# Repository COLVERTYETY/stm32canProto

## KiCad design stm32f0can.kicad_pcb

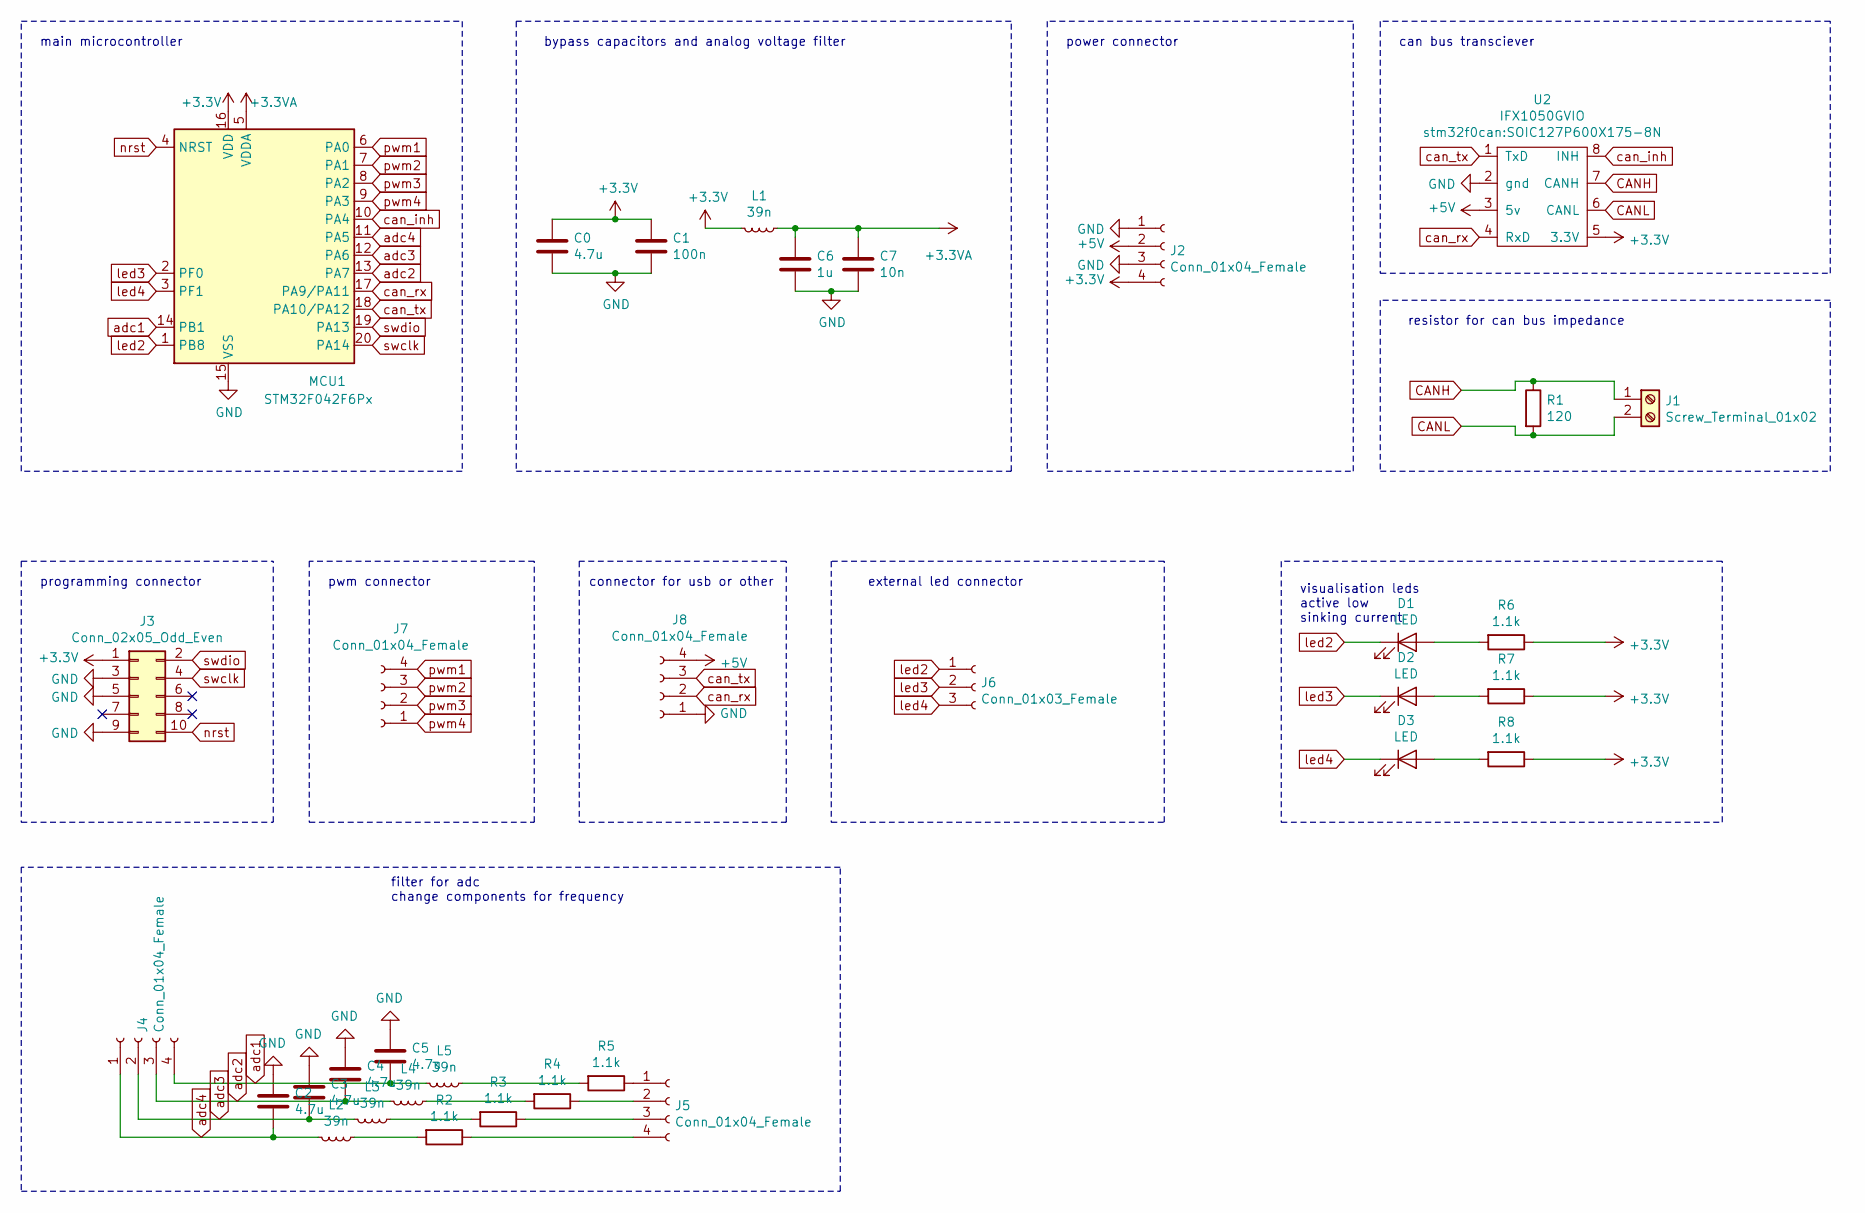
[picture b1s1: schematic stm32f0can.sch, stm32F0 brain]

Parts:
C0, C2, C3, C4, C5: 4.7u; CP_Radial_D6.3mm_P2.50mm
C1: 100n; CP_Radial_D6.3mm_P2.50mm
C6: 1u; CP_Radial_D6.3mm_P2.50mm
C7: 10n; CP_Radial_D6.3mm_P2.50mm
D1, D2, D3: LED; LED_D3.0mm
J1: Screw_Terminal_01x02; TerminalBlock_bornier-2_P5.08mm
J2, J4, J5, J7, J8: Conn_01x04_Female; PinHeader_1x04_P2.54mm_Vertical
J3: Conn_02x05_Odd_Even; PinHeader_2x05_P2.54mm_Vertical
J6: Conn_01x03_Female; PinHeader_1x04_P2.54mm_Vertical
L1, L2, L3, L4, L5: 39n; LairdTech_28C0236-0JW-10
MCU1: STM32F042F6Px; TSSOP-20_4.4x6.5mm_P0.65mm
R1: 120; R_Axial_DIN0204_L3.6mm_D1.6mm_P5.08mm_Vertical
R2, R3, R4, R5, R6, R7, R8: 1.1k; R_Axial_DIN0204_L3.6mm_D1.6mm_P5.08mm_Vertical
U2: IFX1050GVIO; SOIC127P600X175-8N

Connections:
+3.3VA: C6.1, C7.1, L1.1, MCU1.5 (VDDA)
+3V3: C0.1, C1.1, J2.4, J3.1, L1.2, MCU1.16 (VDD), R6.1, R7.1, R8.1, U2.5 (3.3V)
+5V: J2.2, J8.4, U2.3 (5v)
CANH: J1.1, R1.1, U2.7 (CANH)
CANL: J1.2, R1.2, U2.6 (CANL)
GND: C0.2, C1.2, C2.1, C3.1, C4.1, C5.1, C6.2, C7.2, J2.1, J2.3, J3.3, J3.5, J3.9, J8.1, MCU1.15 (VSS), U2.2 (gnd)
unnamed: D1.2 (A), R6.2
unnamed: D2.2 (A), R7.2
unnamed: D3.2 (A), R8.2
unnamed: J5.1, R5.1
unnamed: J5.2, R4.1
unnamed: J5.3, R3.1
unnamed: J5.4, R2.1
unnamed: L2.1, R2.2
unnamed: L3.1, R3.2
unnamed: L4.1, R4.2
unnamed: L5.1, R5.2
adc1: C5.2, J4.4, L5.2, MCU1.14 (PB1)
adc2: C4.2, J4.3, L4.2, MCU1.13 (PA7)
adc3: C3.2, J4.2, L3.2, MCU1.12 (PA6)
adc4: C2.2, J4.1, L2.2, MCU1.11 (PA5)
can_inh: MCU1.10 (PA4), U2.8 (INH)
can_rx: J8.2, MCU1.17 (PA9/PA11), U2.4 (RxD)
can_tx: J8.3, MCU1.18 (PA10/PA12), U2.1 (TxD)
led2: D1.1 (K), J6.1, MCU1.1 (PB8)
led3: D2.1 (K), J6.2, MCU1.2 (PF0)
led4: D3.1 (K), J6.3, MCU1.3 (PF1)
nrst: J3.10, MCU1.4 (NRST)
pwm1: J7.4, MCU1.6 (PA0)
pwm2: J7.3, MCU1.7 (PA1)
pwm3: J7.2, MCU1.8 (PA2)
pwm4: J7.1, MCU1.9 (PA3)
swclk: J3.4, MCU1.20 (PA14)
swdio: J3.2, MCU1.19 (PA13)

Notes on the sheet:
main microcontroller
bypass capacitors and analog voltage filter
power connector
can bus transciever
resistor for can bus impedance
programming connector
pwm connector
connector for usb or other
external led connector
visualisation leds active low sinking current
filter for adc change components for frequency

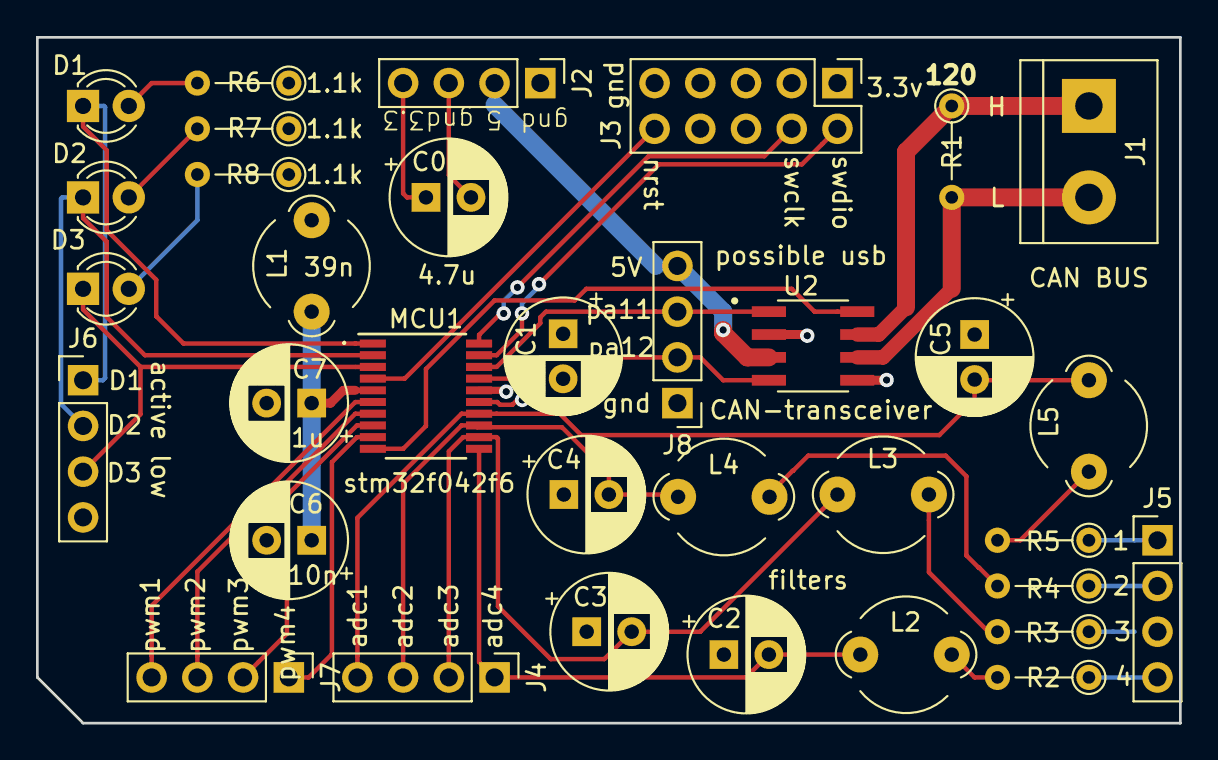
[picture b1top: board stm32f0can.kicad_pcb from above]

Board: 4 copper layers, 63.5 x 38.1 mm, 34 parts (0 on the bottom side), 34 nets.

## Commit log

2020-12-30 added git repo on silklayer
2020-12-30 added images
2020-12-31 added gerbers
